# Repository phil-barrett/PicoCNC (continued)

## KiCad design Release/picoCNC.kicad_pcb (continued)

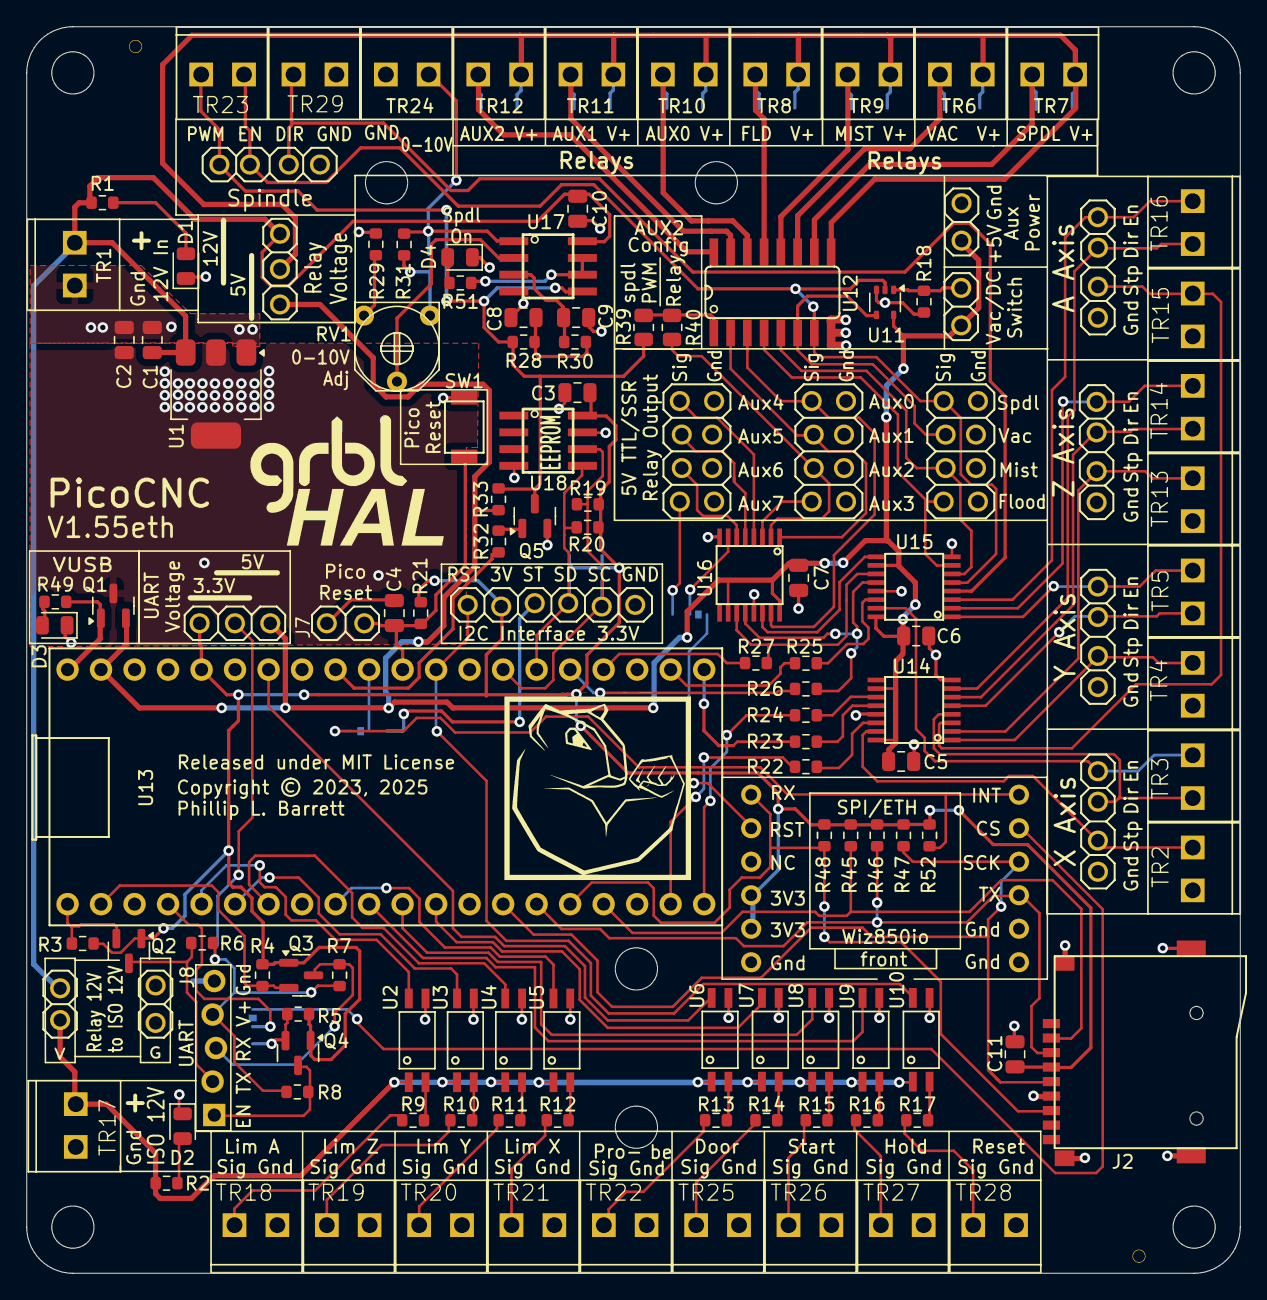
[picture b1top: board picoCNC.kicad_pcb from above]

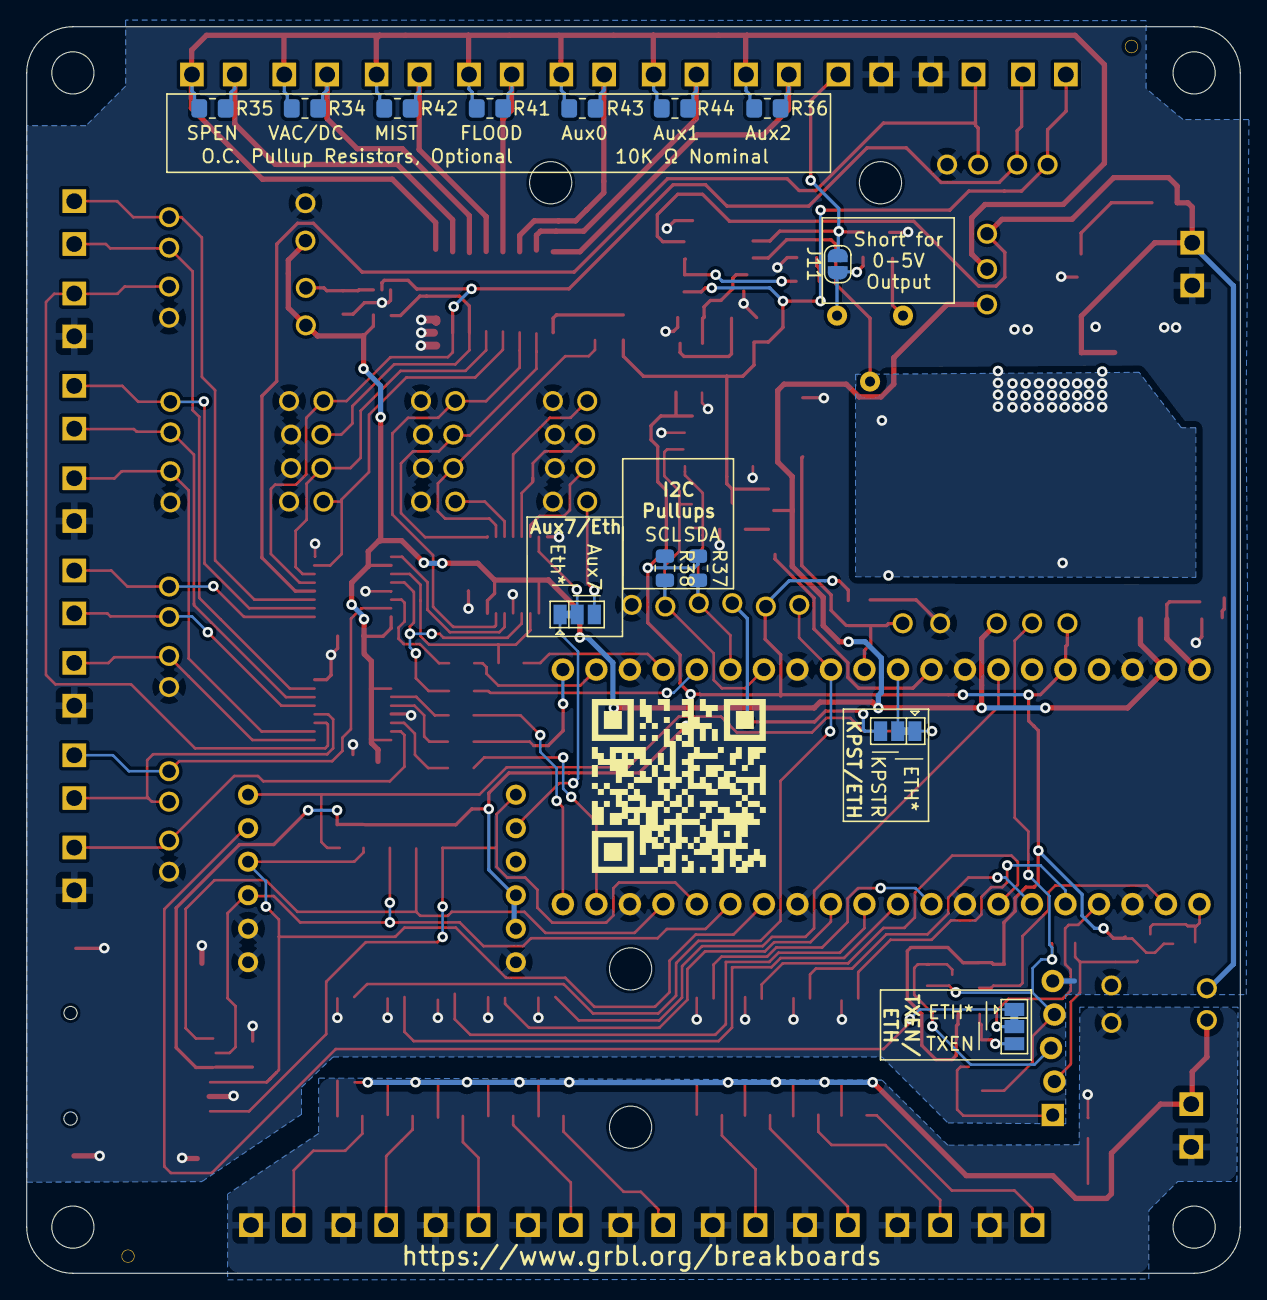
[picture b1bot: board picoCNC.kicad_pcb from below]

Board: 2 copper layers, 92.0 x 94.5 mm, 145 parts (13 on the bottom side), 118 nets.

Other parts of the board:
A: stencil_align_1mm
A#2: stencil_align_1mm

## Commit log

2023-07-17 Add files via upload
    Updated Manual.
2023-07-19 Add files via upload
    New sections added, typos edited, more diagrams and a turtle.
2023-07-21 Add files via upload
    corrected typos, updated networking section.
2023-07-24 Add files via upload
    Further additions and corrections. Rev 0.98
2023-07-24 Add files via upload
    Further additions and correction. Rev 0.98
2023-07-24 Update README.md
    Added feature list to readme
2023-07-24 Add files via upload
    Photo of V1.5 board
2023-07-24 Update README.md
    typos...
2023-07-25 Update README.md
    Reorganized feature list for cleaner presentation.
2023-07-26 Add files via upload
    Updated to V1.0
2023-07-28 Add files via upload
    V1.01 - Updated fw install process and initial Grbl Settings. Added errata.
2023-08-03 Update README.md
    Now available!
2023-08-06 Update README.md
    minor edits
2023-08-25 Add files via upload
    Update to include more assembly photos, document V1.52 differences and minor typo corrections.
2023-08-25 Update README.md
    minor typo corrections
2023-08-30 Add files via upload
    Add PSU warnings.
2023-09-05 Add files via upload
    PicoCNC V1.52 3D Model in step format.
2023-09-05 Add files via upload
    Added missing components.
2023-09-17 Add files via upload
    Typo fixes, clarifications added.
2023-11-08 Added V1.53eth features
2023-11-08 Update to reflect V1.53eth features
2023-11-08 Update README.md
    typo fix
2023-11-14 Typos and clarifications.
2023-11-14 Update README.md
    Added link to User Manual.
2023-11-17 Add files via upload
    updated photos and added clarification text
2023-11-17 Add files via upload
    V1.53eth photo
2023-11-17 Update README.md
    updated photo to V1.53eth
2023-12-10 Add files via upload
    Added location diagram, minor typos.
